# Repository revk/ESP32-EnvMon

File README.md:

# ESP32-EnvMon

Now at [Codeberg](https://codeberg.org/RevK/ESP32-EnvMon)

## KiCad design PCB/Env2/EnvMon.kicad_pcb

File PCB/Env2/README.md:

# EnvMon

These files are for use in [KiCad](https://www.kicad.org).

## Trademark

This is an open source project, but bear in mind you cannot sell boards bearing the Andrews & Arnold Ltd name, the A&A logo, the registered trademark AJK logo, or the GS1 allocated EANs assigned to Andrews & Arnold Ltd.

## Images

*Auto generated 2025-05-04T08:00:31*

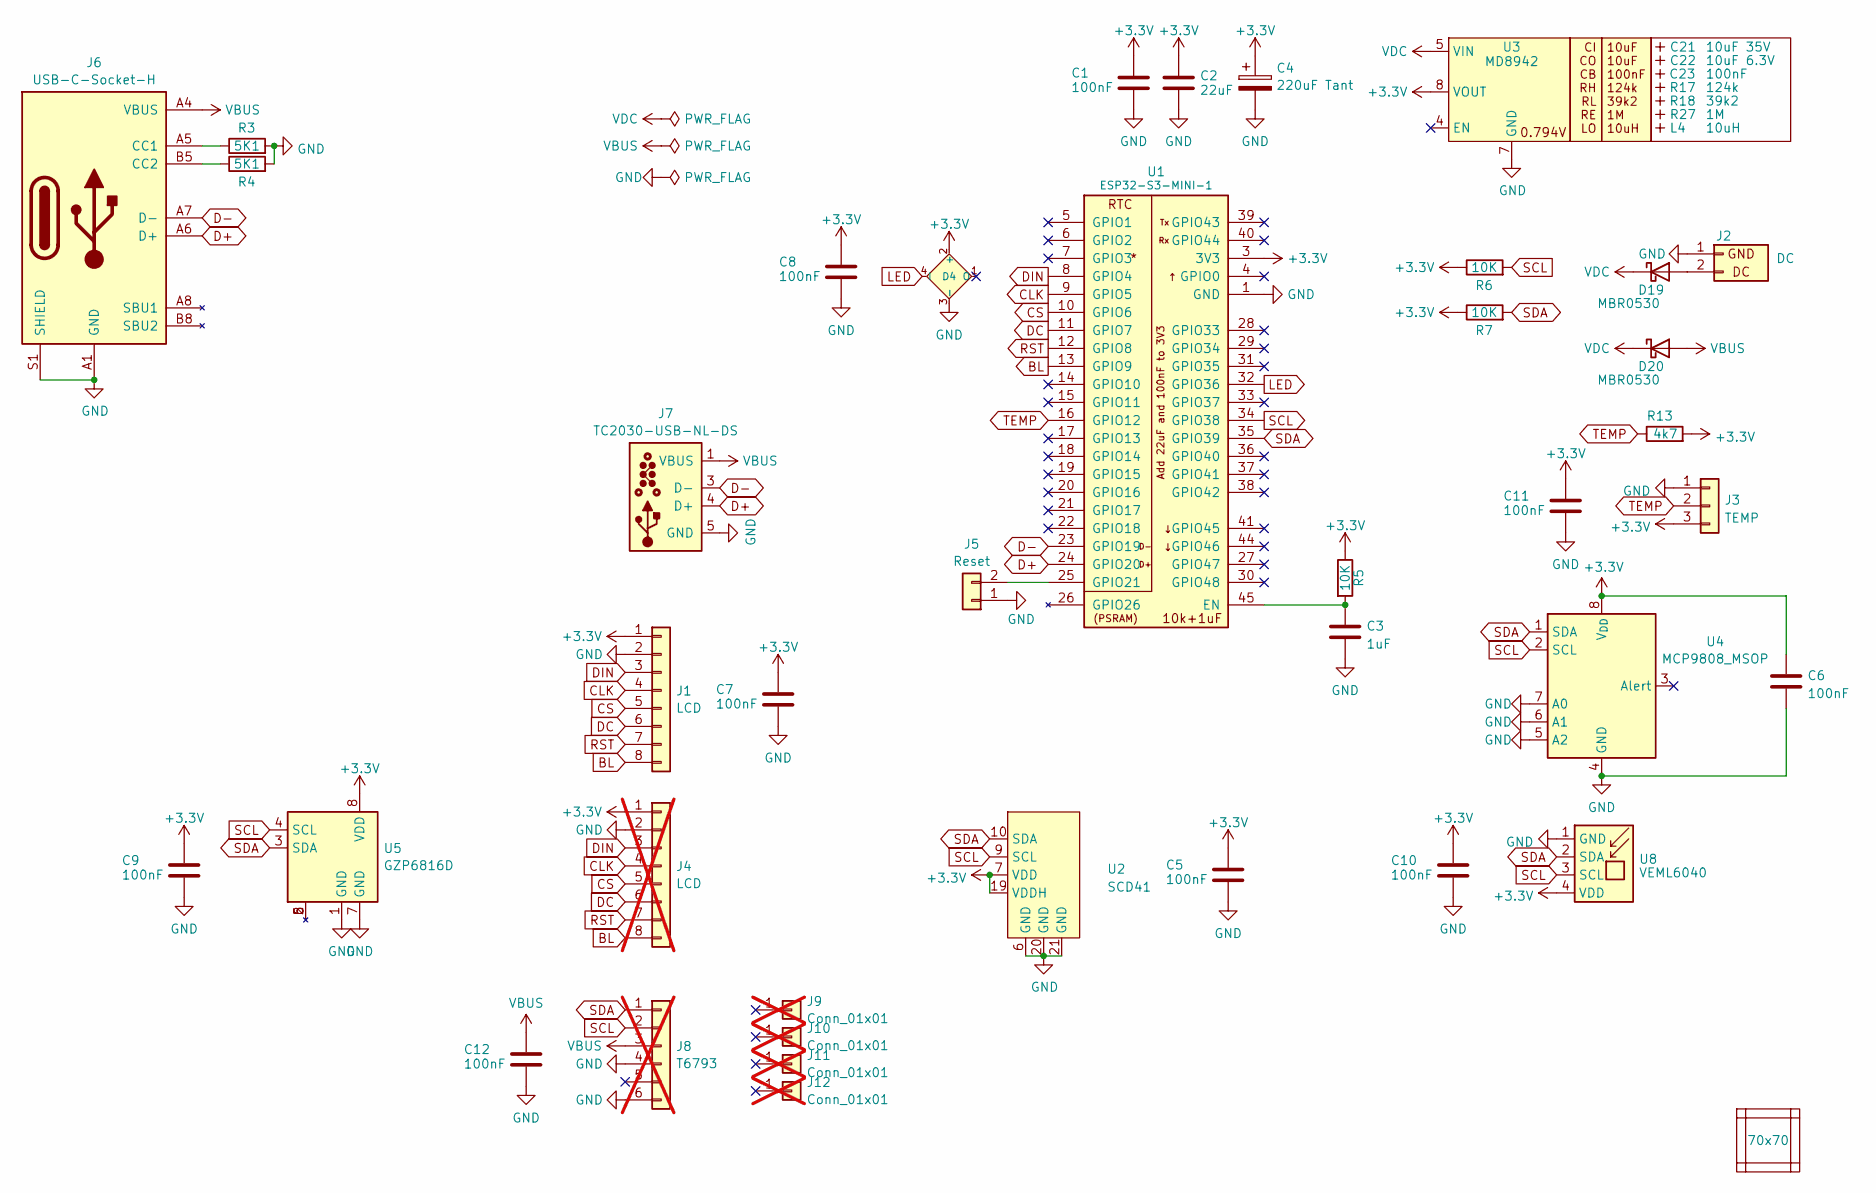
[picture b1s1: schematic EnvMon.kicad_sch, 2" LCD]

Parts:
C1, C5, C6, C7, C8, C9, C10, C11, C12: 100nF; C_0402
C2: 22uF; C_0402
C3: 1uF; C_0402
C4: 220uF Tant; CP_EIA-3528-21_Kemet-B; MPN C122649
C21: 10uF 35V; C_0603_; MPN C194427
C22: 10uF 6.3V; C_0603_; MPN C1691
C23: 100nF; C_0603_
D4: XL-1010RGBC-WS2812B; SMD1010-Side2; MPN C5349953
D19, D20: MBR0530; D_SOD-123; MPN C5204746
J1: LCD; LCD2; MPN C42380985
J2: DC; WAGO-2060-452-998-404; MPN C2765055
J3: TEMP; WAGO-2060-453-998-404; MPN C2765056
J4: LCD; PinHeader_1x08_P2.54mm_Vertical; MPN C42380985; not fitted
J5: Reset; AA-Pad
J6: USB-C-Socket-H; MPN C709357
J7: TC2030-USB-NL-DS; Tag-Connect_TC2030-IDC-NL_2x03_P1.27mm_Vertical
J8: T6793; PinHeader_1x06_P2.54mm_Vertical; not fitted
J9, J10, J11, J12: Conn_01x01; PinHeader_1x01_P2.54mm_Vertical; not fitted
L4: 10uH; L_4x4_; MPN C167879
PCB1: 70x70; PCB7070
R3, R4: 5K1; R_0402
R5, R6, R7: 10K; R_0402
R13: 4k7; R_0402
R17: 124k; R_0402_
R18: 39k2; R_0402_
R27: 1M; R_0402_
U1: ESP32-S3-MINI-1; MPN C3013941
U2: SCD41; MPN C3659294
U3: MD8942; SOT-23-6-MD8942; MPN C2684786
U4: MCP9808_MSOP; MSOP-8_3x3mm_P0.65mm-SIde; MPN C94847
U5: GZP6816D; Bosch_LGA-8_2x2.5mm_P0.65mm_ClockwisePinNumbering; MPN C3038127
U8: VEML6040; VEML6040-Side; MPN C78465
V1, V2, V3, V4: VCUT70

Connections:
+3.3V: C1.1, C2.1, C4.1, C5.1, C6.1, C7.1, C8.1, C9.1, C10.1, C11.1, D4.2 (+), J1.1, J3.3, J4.1, R5.1, R6.1, R7.1, R13.2, U1.3 (3V3), U2.7 (VDD), U2.19 (VDDH), U3.8 (VOUT), U4.8 (V_{DD}), U5.8 (VDD), U8.4 (VDD)
BL: J1.8, J4.8, U1.13 (GPIO9)
CLK: J1.4, J4.4, U1.9 (GPIO5)
CS: J1.5, J4.5, U1.10 (GPIO6)
D+: J6.A6 (D+), J6.B6 (D+), J7.4 (D+), U1.24 (GPIO20)
D-: J6.A7 (D-), J6.B7 (D-), J7.2 (NC), J7.3 (D-), J7.6 (NC), U1.23 (GPIO19)
DC: J1.6, J4.6, U1.11 (GPIO7)
DIN: J1.3, J4.3, U1.8 (GPIO4)
GND: C1.2, C2.2, C3.2, C4.2, C5.2, C6.2, C7.2, C8.2, C9.2, C10.2, C11.2, C12.2, D4.3 (-), J1.2, J2.1 (GND), J3.1, J4.2, J5.1, J6.A1 (GND), J6.A12 (GND), J6.B1 (GND), J6.B12 (GND), J6.S1 (SHIELD), J7.5 (GND), J8.4, J8.6, R3.2, R4.2, U1.1 (GND), U1.2 (GND), U1.42 (GND), U1.43 (GND), U1.46 (GND), U1.47 (GND), U1.48 (GND), U1.49 (GND), U1.50 (GND), U1.51 (GND), U1.52 (GND), U1.53 (GND), U1.54 (GND), U1.55 (GND), U1.56 (GND), U1.57 (GND), U1.58 (GND), U1.59 (GND), U1.60 (GND), U1.61 (GND), U1.62 (GND), U1.63 (GND), U1.64 (GND), U1.65 (GND), U2.6 (GND), U2.20 (GND), U2.21 (GND), U3.2 (GND), U3.7 (GND), U4.4 (GND), U4.5 (A2), U4.6 (A1), U4.7 (A0), U5.1 (GND), U5.7 (GND), U8.1 (GND)
LED: D4.4 (I), U1.32 (GPIO36)
unnamed: D19.2 (A), J2.2 (DC)
unnamed: J5.2, U1.25 (GPIO21)
unnamed: J6.A5 (CC1), R3.1
unnamed: J6.B5 (CC2), R4.1
unnamed: C3.1, R5.2, U1.45 (EN)
RST: J1.7, J4.7, U1.12 (GPIO8)
SCL: J8.2, R6.2, U1.34 (GPIO38), U2.9 (SCL), U4.2 (SCL), U5.4 (SCL), U8.3 (SCL)
SDA: J8.1, R7.2, U1.35 (GPIO39), U2.10 (SDA), U4.1 (SDA), U5.3 (SDA), U8.2 (SDA)
TEMP: J3.2, R13.1, U1.16 (GPIO12)
VBUS: C12.1, D20.2 (A), J6.A4 (VBUS), J6.A9 (VBUS), J6.B4 (VBUS), J6.B9 (VBUS), J7.1 (VBUS), J8.3
VDC: D19.1 (K), D20.1 (K), U3.5 (VIN)

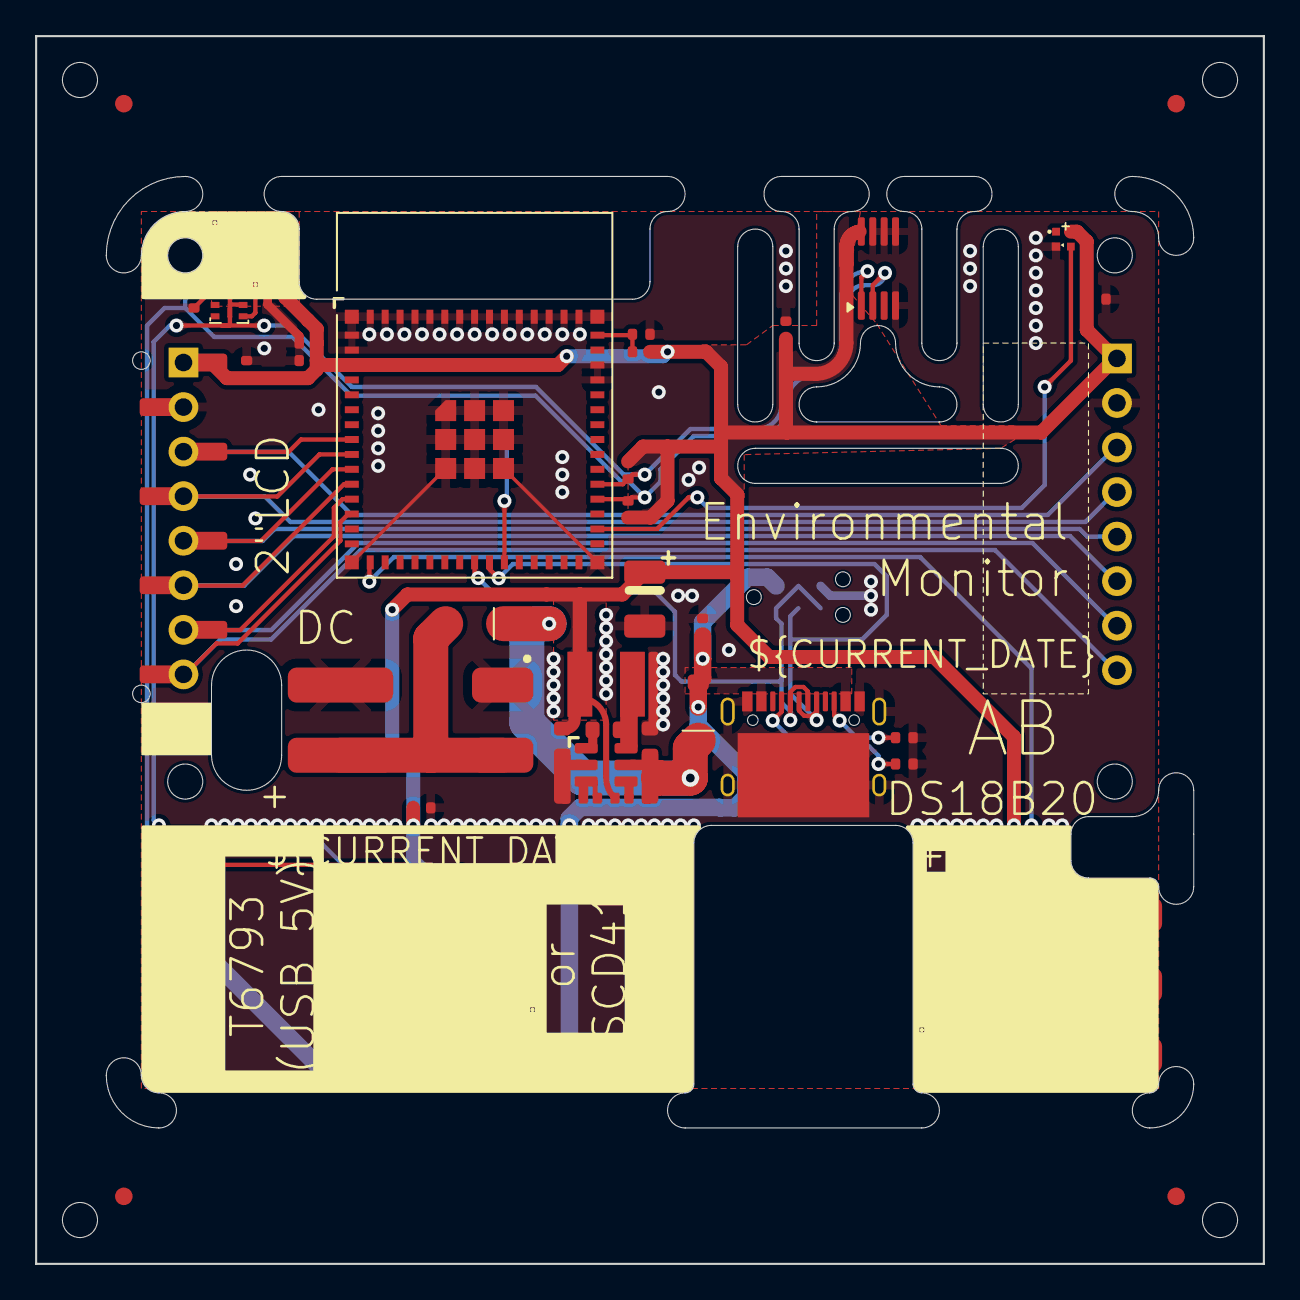
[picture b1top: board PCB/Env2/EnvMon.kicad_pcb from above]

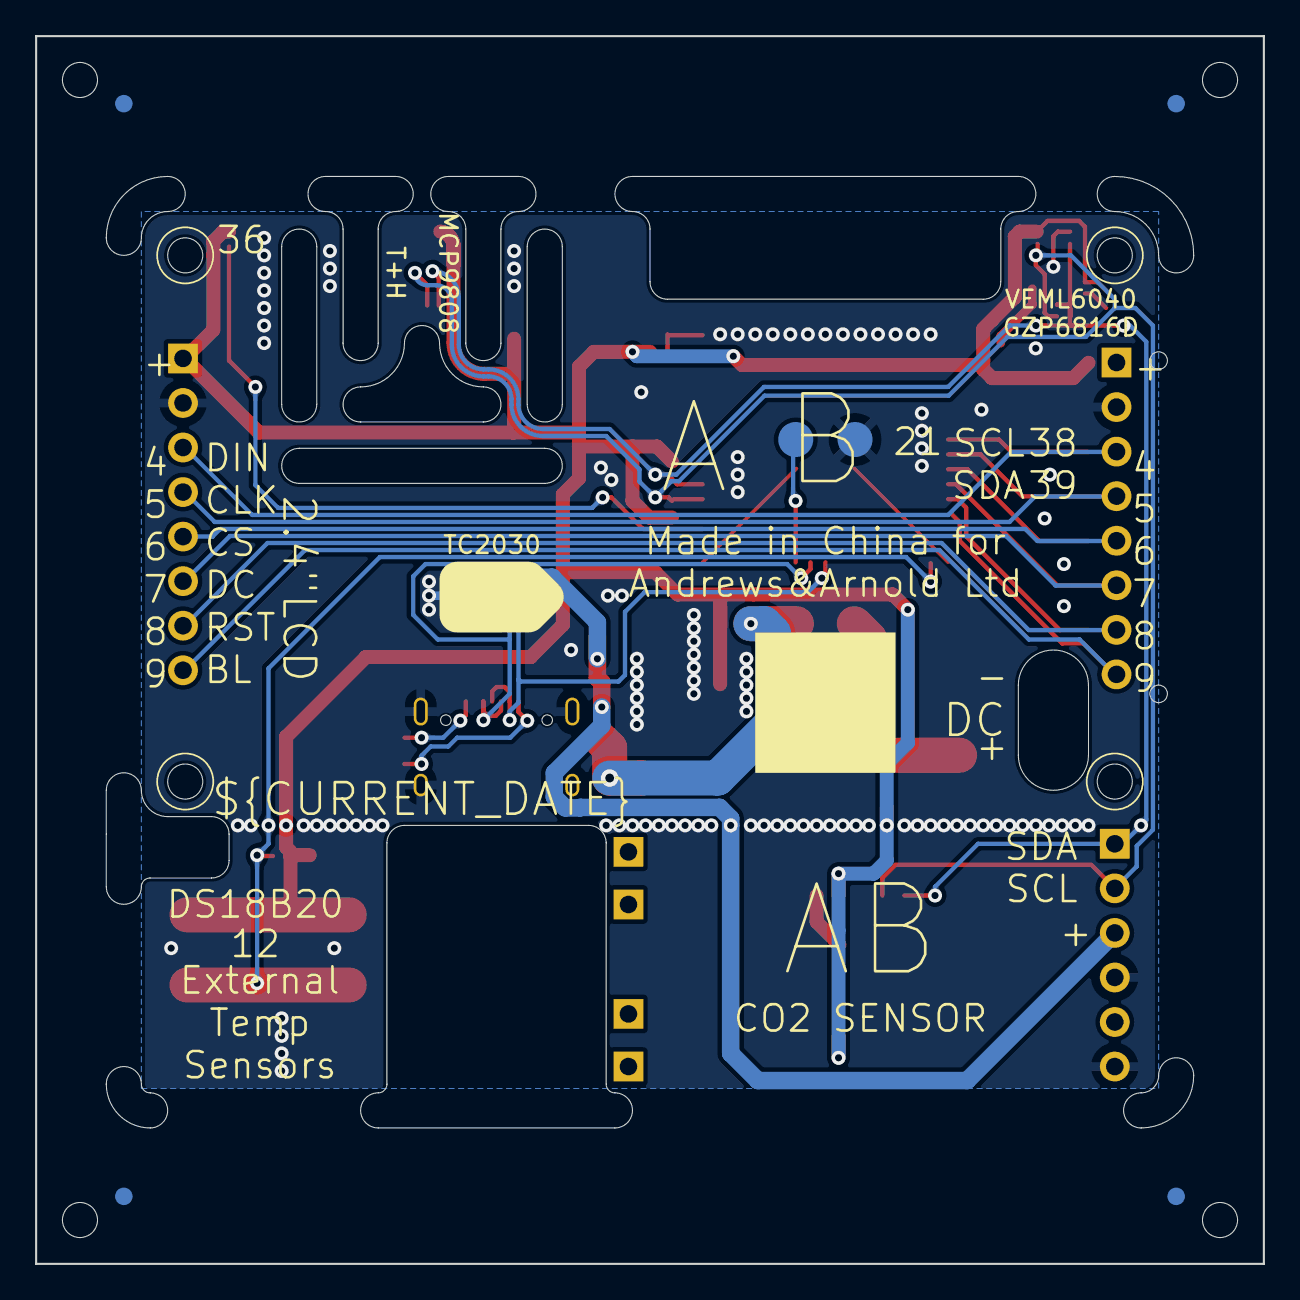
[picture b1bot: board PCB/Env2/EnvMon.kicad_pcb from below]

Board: 2 copper layers, 70.0 x 70.0 mm, 51 parts (3 on the bottom side), 21 nets.

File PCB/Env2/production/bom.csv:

Designator,Footprint,Quantity,Value,LCSC Part #
"C1, C10, C11, C12, C5, C6, C7, C8, C9",C_0402,9,100nF,
C2,C_0402,1,22uF,
C21,C_0603_,1,10uF 35V,C194427
C22,C_0603_,1,10uF 6.3V,C1691
C23,C_0603_,1,100nF,
C3,C_0402,1,1uF,
C4,CP_EIA-3528-21_Kemet-B,1,220uF Tant,C122649
"D19, D20",D_SOD-123,2,MBR0530,C5204746
D4,SMD1010,1,XL-1010RGBC-WS2812B,C5349953
J1,LCD2,1,LCD,C42380985
J2,WAGO-2060-452-998-404,1,DC,C2765055
J3,WAGO-2060-453-998-404,1,TEMP,C2765056
J6,USB-C-Socket-H,1,USB-C-Socket-H,C709357
L4,L_4x4_,1,10uH,C167879
R13,R_0402,1,4k7,
R17,R_0402_,1,124k,
R18,R_0402_,1,39k2,
R27,R_0402_,1,1M,
"R3, R4",R_0402,2,5K1,
"R5, R6, R7",R_0402,3,10K,
U1,ESP32-S3-MINI-1,1,ESP32-S3-MINI-1,C3013941
U2,SCD41,1,SCD41,C3659294
U3,SOT-23-6-MD8942,1,MD8942,C2684786
U4,MSOP-8_3x3mm_P0.65mm,1,MCP9808_MSOP,C94847
U5,Bosch_LGA-8_2x2.5mm_P0.65mm_ClockwisePinNumbering,1,GZP6816D,C3038127
U8,VEML6040,1,VEML6040,C78465

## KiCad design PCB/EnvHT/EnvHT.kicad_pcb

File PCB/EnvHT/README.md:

# EnvHT

These files are for use in [KiCad](https://www.kicad.org).

## Trademark

This is an open source project, but bear in mind you cannot sell boards bearing the Andrews & Arnold Ltd name, the A&A logo, the registered trademark AJK logo, or the GS1 allocated EANs assigned to Andrews & Arnold Ltd.

## Images

*Auto generated 2025-05-04T08:03:03*

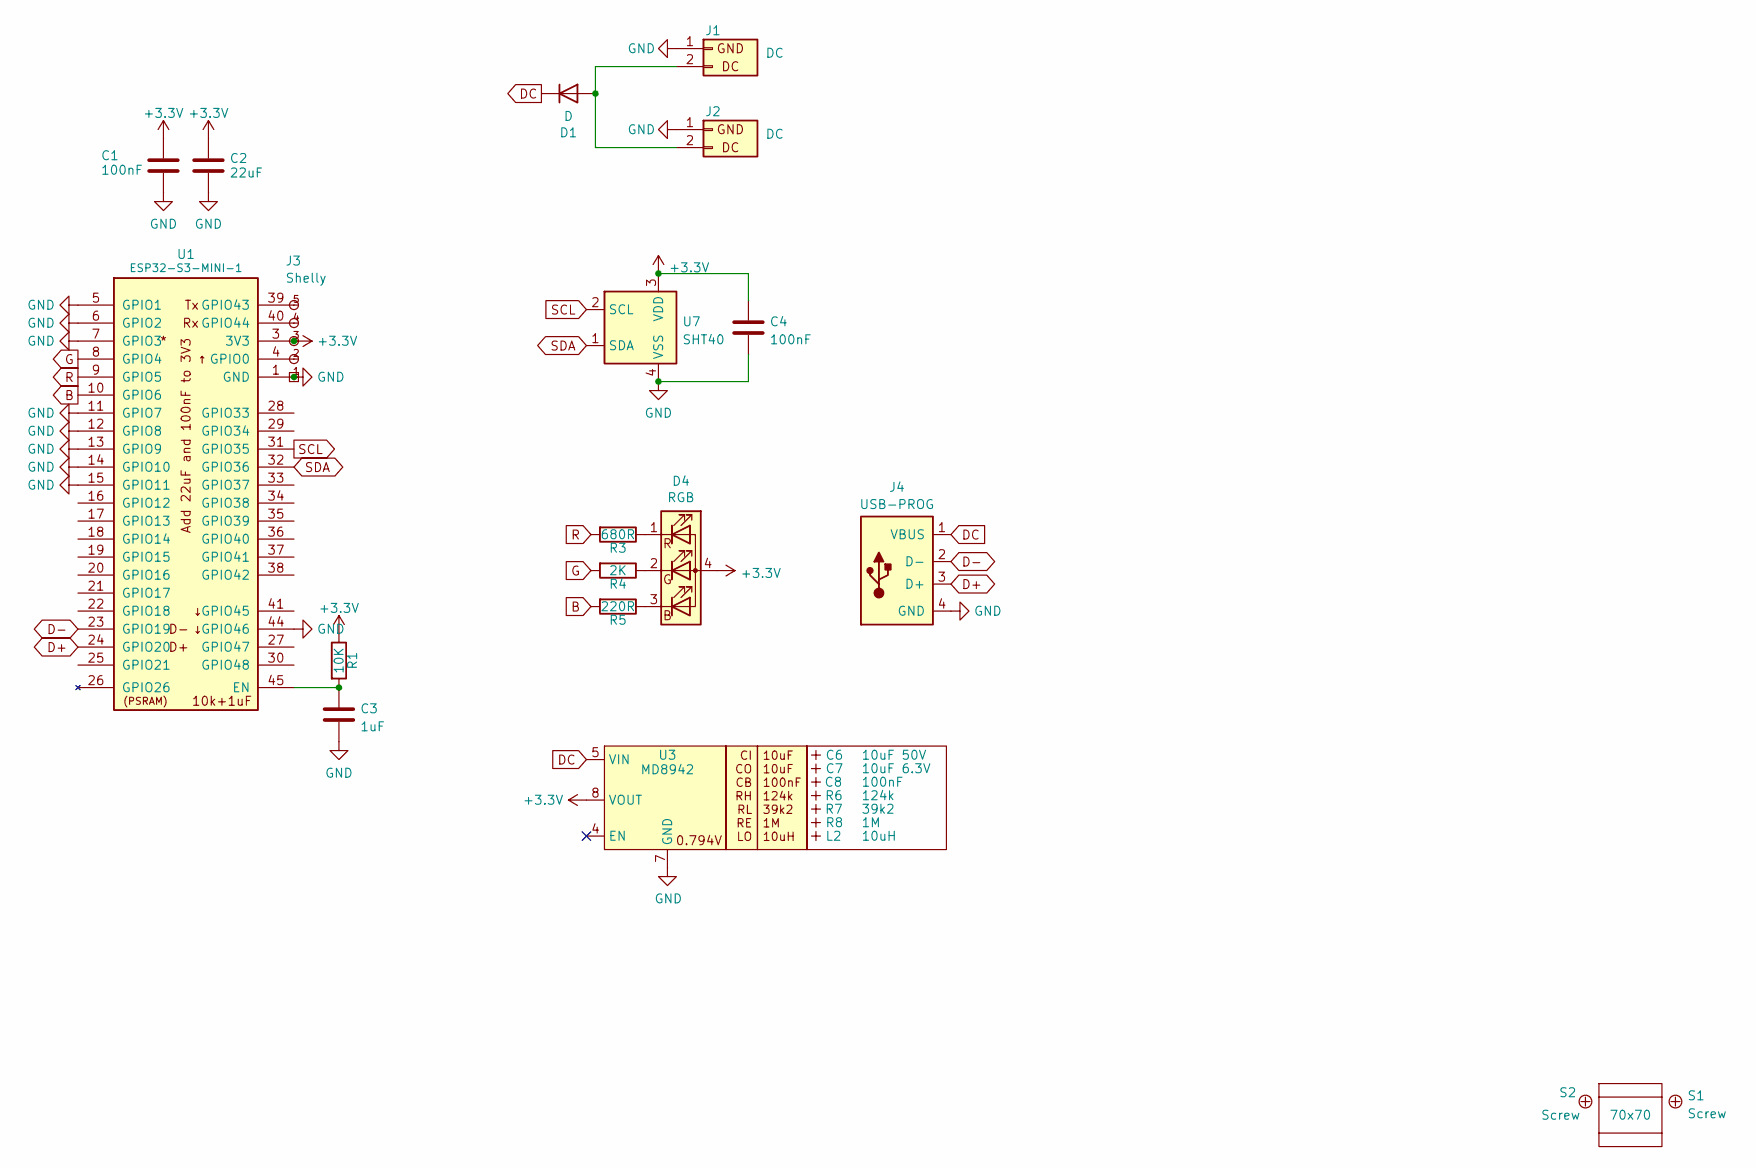
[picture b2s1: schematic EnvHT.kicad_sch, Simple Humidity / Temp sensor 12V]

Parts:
C1, C4: 100nF; C_0402
C2: 22uF; C_0603
C3: 1uF; C_0402
C6: 10uF 50V; C_0603_; MPN C1591
C7: 10uF 6.3V; C_0603_; MPN C1691
C8: 100nF; C_0603_
D1: D; D_SOD-123; MPN C1884542
D4: RGB; LED-RGB-1.6x1.6; Part No APTF1616LSEEZGKQBKC
J1, J2: DC; PTSM-HH1-2-RA
J3: Shelly
J4: USB-PROG
L2: 10uH; L_4x4_
PCB1: 70x70; PCB7070
R1: 10K; R_0402
R3: 680R; R_0402
R4: 2K; R_0402
R5: 220R; R_0402
R6: 124k; R_0402_
R7: 39k2; R_0402_
R8: 1M; R_0402_
S1, S2: Screw
U1: ESP32-S3-MINI-1; MPN C3013941
U3: MD8942; SOT-23-6-MD8942; MPN C2684786
U7: SHT40; Sensirion_DFN-4_1.5x1.5mm_P0.5mm_SHT4x; MPN C2909890
V2, V3: VCUT70

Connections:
+3.3V: C1.1, C2.1, C4.1, D4.4 (A), J3.3 (3V3), R1.1, U1.3 (3V3), U3.8 (VOUT), U7.3 (VDD)
B: R5.2, U1.10 (GPIO6)
D+: J4.3 (D+), U1.24 (GPIO20)
D-: J4.2 (D-), U1.23 (GPIO19)
DC: D1.1 (K), J4.1 (VBUS), U3.5 (VIN)
G: R4.2, U1.8 (GPIO4)
GND: C1.2, C2.2, C3.2, C4.2, J1.1 (GND), J2.1 (GND), J3.1 (GND), J4.4 (GND), U1.1 (GND), U1.2 (GND), U1.5 (GPIO1), U1.6 (GPIO2), U1.7 (GPIO3), U1.11 (GPIO7), U1.12 (GPIO8), U1.13 (GPIO9), U1.14 (GPIO10), U1.15 (GPIO11), U1.42 (GND), U1.43 (GND), U1.44 (GPIO46), U1.46 (GND), U1.47 (GND), U1.48 (GND), U1.49 (GND), U1.50 (GND), U1.51 (GND), U1.52 (GND), U1.53 (GND), U1.54 (GND), U1.55 (GND), U1.56 (GND), U1.57 (GND), U1.58 (GND), U1.59 (GND), U1.60 (GND), U1.61 (GND), U1.62 (GND), U1.63 (GND), U1.64 (GND), U1.65 (GND), U3.2 (GND), U3.7 (GND), U7.4 (VSS)
unnamed: D1.2 (A), J1.2 (DC), J2.2 (DC)
unnamed: D4.3 (BK), R5.1
unnamed: D4.2 (GK), R4.1
unnamed: D4.1 (RK), R3.1
unnamed: J3.2 (0), U1.4 (GPIO0)
unnamed: J3.4 (Rx), U1.40 (GPIO44)
unnamed: J3.5 (Tx), U1.39 (GPIO43)
unnamed: C3.1, R1.2, U1.45 (EN)
R: R3.2, U1.9 (GPIO5)
SCL: U1.31 (GPIO35), U7.2 (SCL)
SDA: U1.32 (GPIO36), U7.1 (SDA)

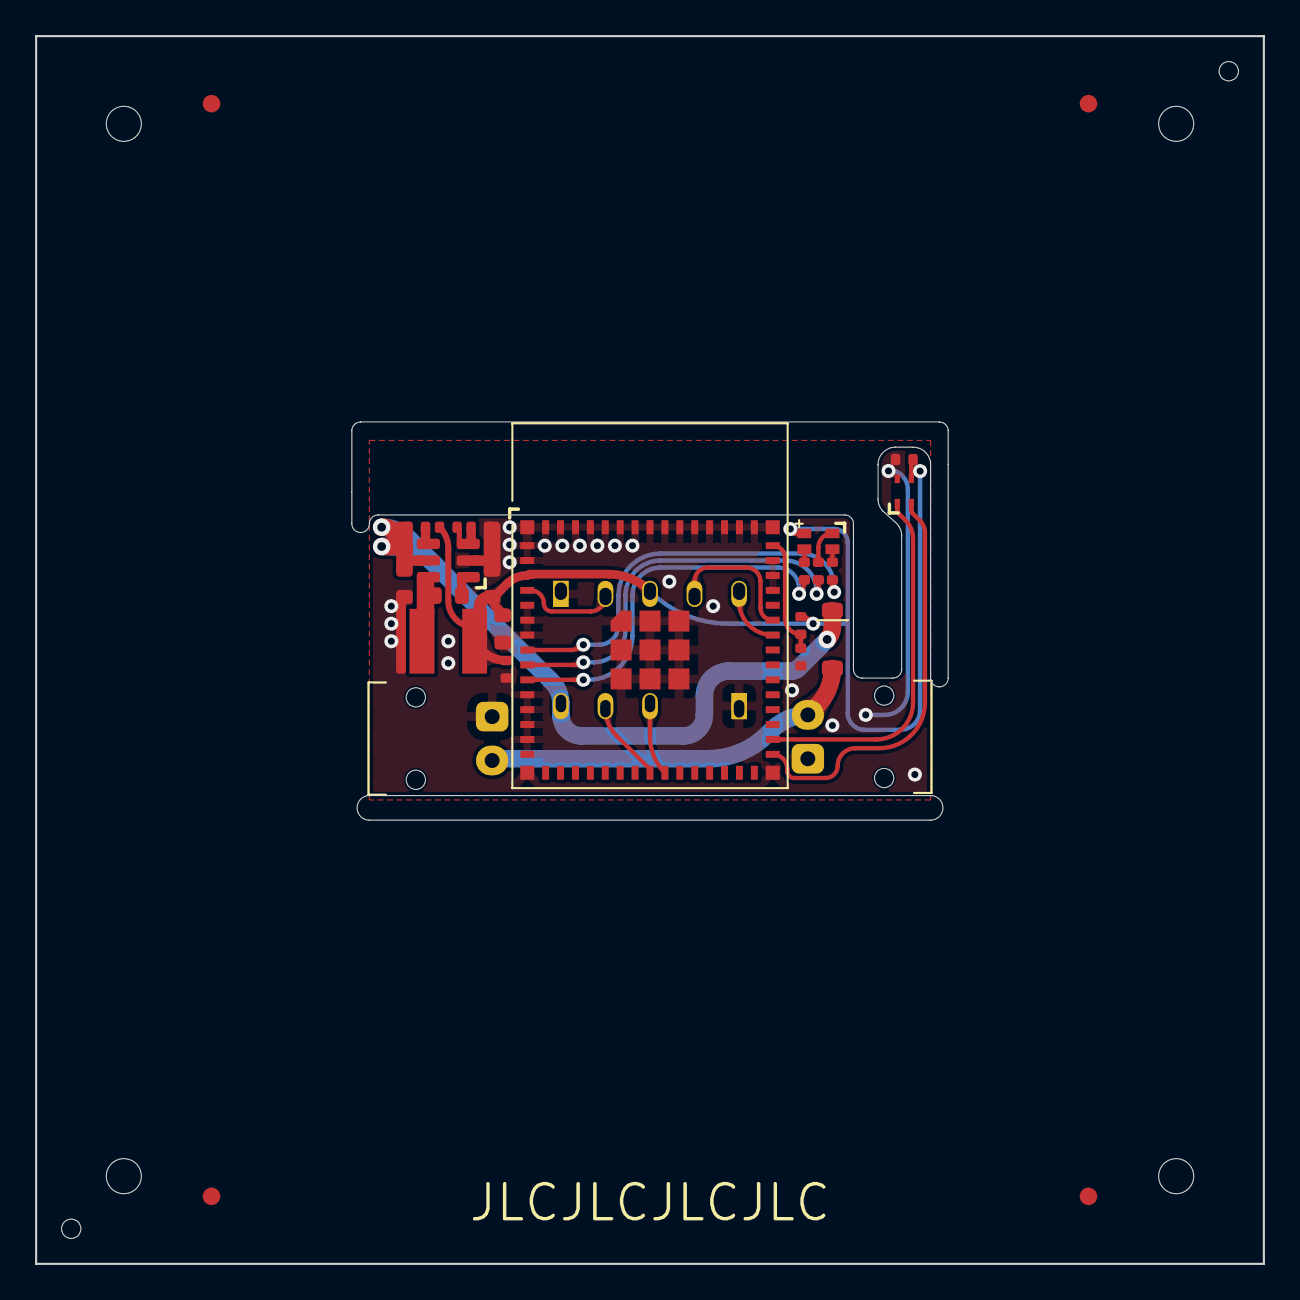
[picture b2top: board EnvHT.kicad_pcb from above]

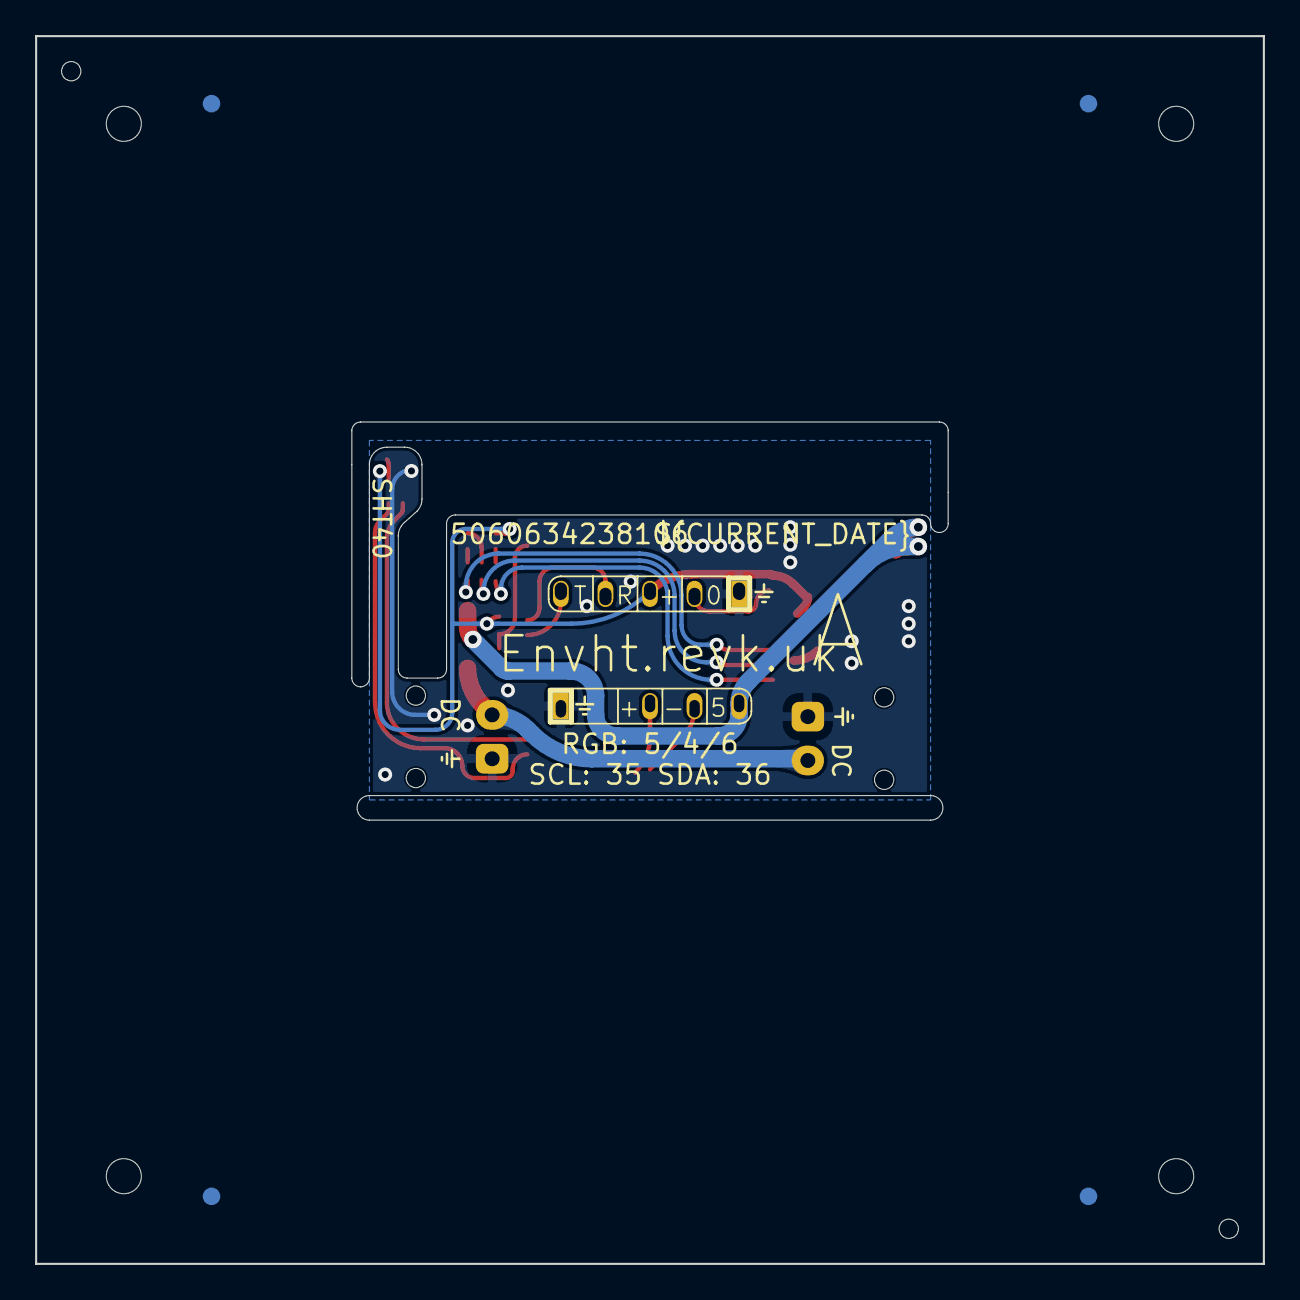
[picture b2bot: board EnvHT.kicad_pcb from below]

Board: 2 copper layers, 70.0 x 70.0 mm, 29 parts (2 on the bottom side), 18 nets.

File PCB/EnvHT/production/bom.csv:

Designator,Footprint,Quantity,Value,LCSC Part #
"C1, C4",C_0402,2,100nF,
C2,C_0603,1,22uF,
C3,C_0402,1,1uF,
C6,C_0603_,1,10uF 50V,C1591
C7,C_0603_,1,10uF 6.3V,C1691
C8,C_0603_,1,100nF,
D1,D_SOD-123,1,D,C1884542
D4,LED-RGB-1.6x1.6,1,RGB,C264508
J4,USB-PROG,1,USB-PROG,
L2,L_4x4_,1,10uH,
R1,R_0402,1,10K,
R3,R_0402,1,680R,
R4,R_0402,1,2K,
R5,R_0402,1,220R,
R6,R_0402_,1,124k,
R7,R_0402_,1,39k2,
R8,R_0402_,1,1M,
U1,ESP32-S3-MINI-1,1,ESP32-S3-MINI-1,C3013941
U3,SOT-23-6-MD8942,1,MD8942,C2684786
U7,Sensirion_DFN-4_1.5x1.5mm_P0.5mm_SHT4x,1,SHT40,C2909890

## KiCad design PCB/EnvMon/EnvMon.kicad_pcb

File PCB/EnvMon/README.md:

# EnvMon

These files are for use in [KiCad](https://www.kicad.org).

## Trademark

This is an open source project, but bear in mind you cannot sell boards bearing the Andrews & Arnold Ltd name, the A&A logo, the registered trademark AJK logo, or the GS1 allocated EANs assigned to Andrews & Arnold Ltd.

## Images

*Auto generated 2025-05-04T08:05:16*

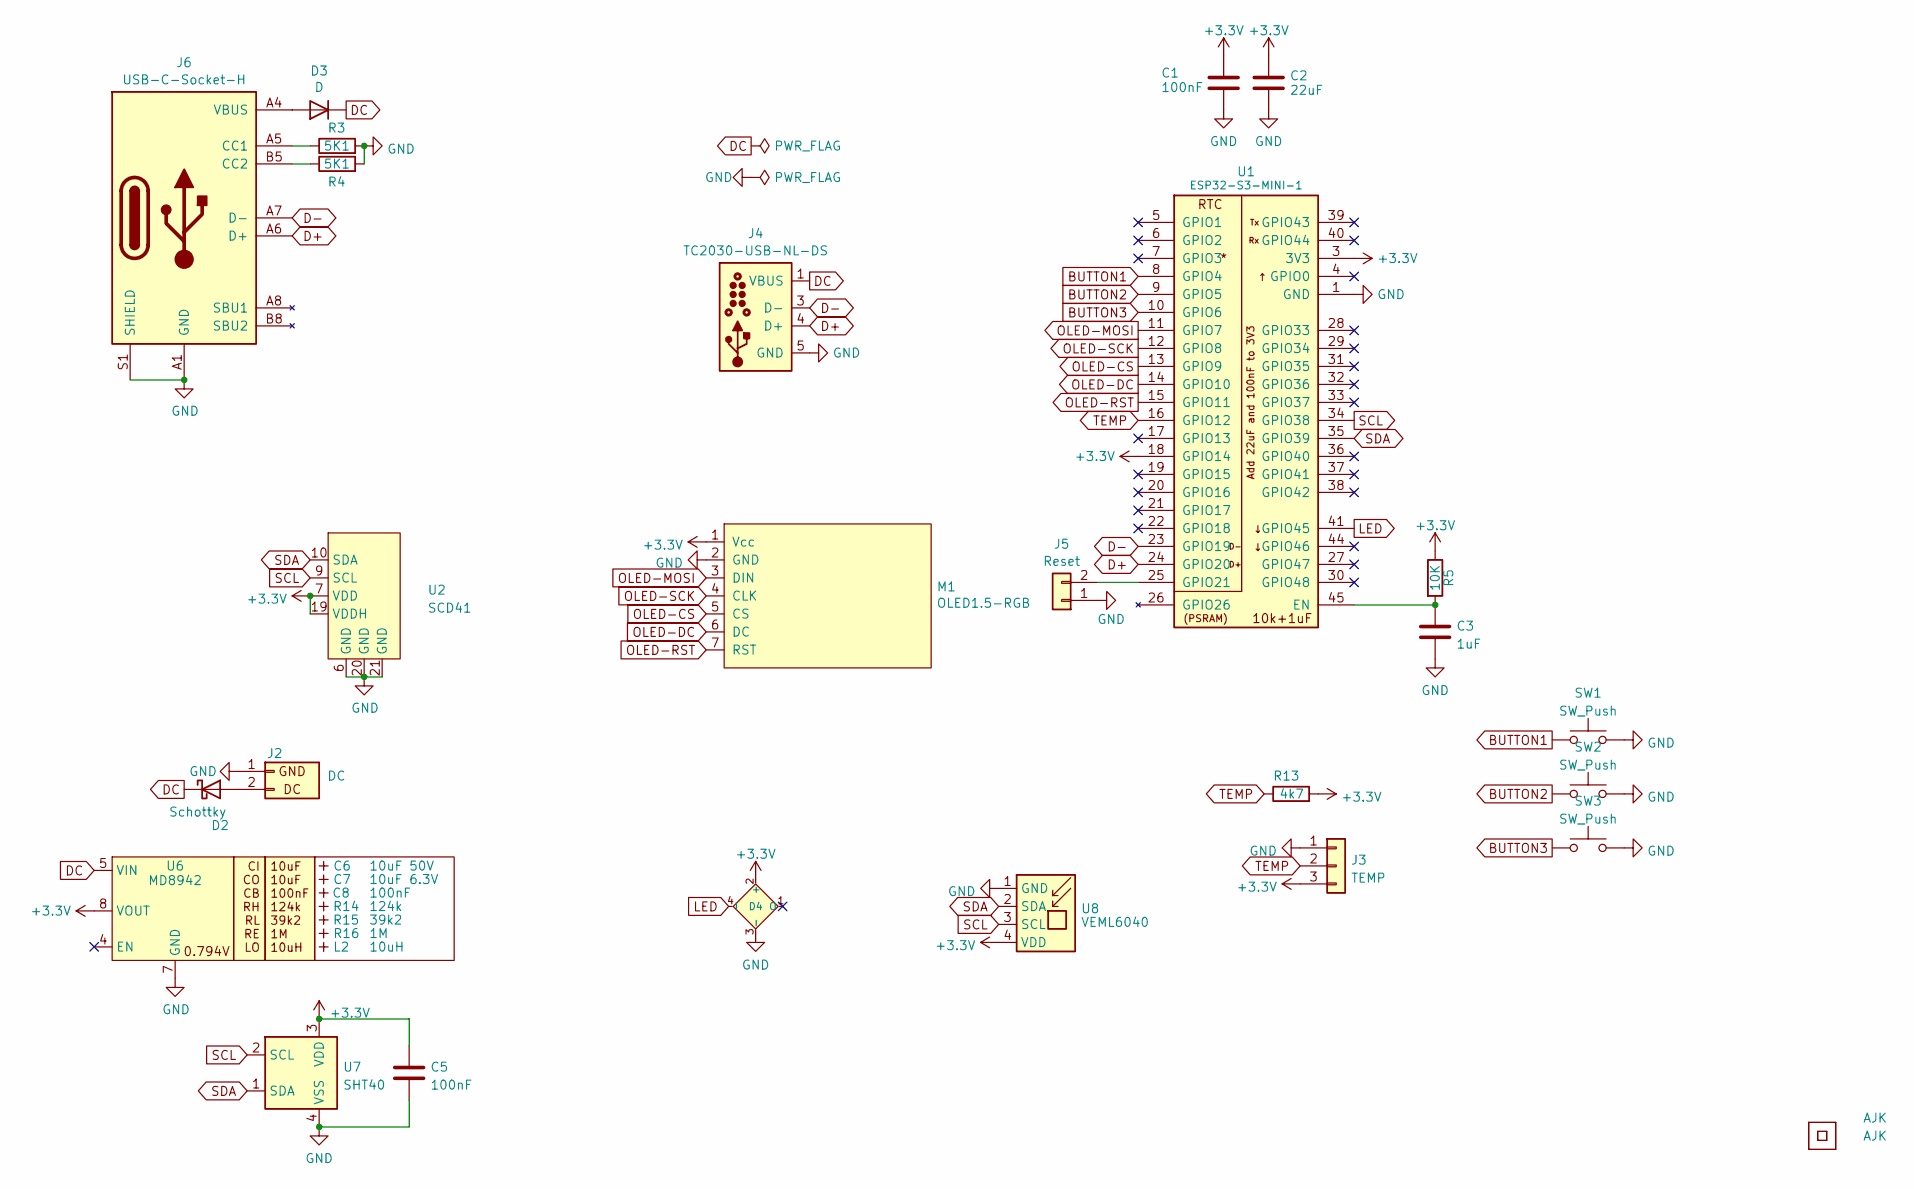
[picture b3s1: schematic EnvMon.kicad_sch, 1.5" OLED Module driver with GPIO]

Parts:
C1, C5: 100nF; C_0402
C2: 22uF; C_0402
C3: 1uF; C_0402
C6: 10uF 50V; C_0603_; MPN C1591
C7: 10uF 6.3V; C_0603_; MPN C1691
C8: 100nF; C_0603_
D2: Schottky; D_1206; MPN C143805
D3: D; D_SOD-123; MPN C1884542
D4: XL-1010RGBC-WS2812B; SMD1010; MPN C5349953
J2: DC; WAGO-2060-452-998-404
J3: TEMP; WAGO-2060-453-998-404
J4: TC2030-USB-NL-DS; Tag-Connect_TC2030-IDC-NL_2x03_P1.27mm_Vertical
J5: Reset; AA-Pad
J6: USB-C-Socket-H; MPN C709357
L2: 10uH; L_4x4_
Logo1, Logo2: AJK
M1: OLED1.5-RGB
R3, R4: 5K1; R_0402
R5: 10K; R_0402
R13: 4k7; R_0402
R14: 124k; R_0402_
R15: 39k2; R_0402_
R16: 1M; R_0402_
SW1, SW2, SW3: SW_Push; SW_PUSH_6mm_H13mm
U1: ESP32-S3-MINI-1; MPN C3013941
U2: SCD41
U5: QR; QR-ENVMON
U6: MD8942; SOT-23-6-MD8942; MPN C2684786
U7: SHT40; Sensirion_DFN-4_1.5x1.5mm_P0.5mm_SHT4x; MPN C2909890
U8: VEML6040; MPN C78465

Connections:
+3.3V: C1.1, C2.1, C5.1, D4.2 (+), J3.3, M1.1 (Vcc), R5.1, R13.2, U1.3 (3V3), U1.18 (GPIO14), U2.7 (VDD), U2.19 (VDDH), U6.8 (VOUT), U7.3 (VDD), U8.4 (VDD)
BUTTON1: SW1.1, U1.8 (GPIO4)
BUTTON2: SW2.1, U1.9 (GPIO5)
BUTTON3: SW3.1, U1.10 (GPIO6)
D+: J4.4 (D+), J6.A6 (D+), J6.B6 (D+), U1.24 (GPIO20)
D-: J4.3 (D-), J6.A7 (D-), J6.B7 (D-), U1.23 (GPIO19)
DC: D2.1 (K), D3.1 (K), J4.1 (VBUS), J4.2 (VBUS), U6.5 (VIN)
GND: C1.2, C2.2, C3.2, C5.2, D4.3 (-), J2.1 (GND), J3.1, J4.5 (GND), J4.6 (GND), J5.1, J6.A1 (GND), J6.A12 (GND), J6.B1 (GND), J6.B12 (GND), J6.S1 (SHIELD), M1.2 (GND), R3.2, R4.2, SW1.2, SW2.2, SW3.2, U1.1 (GND), U1.2 (GND), U1.42 (GND), U1.43 (GND), U1.46 (GND), U1.47 (GND), U1.48 (GND), U1.49 (GND), U1.50 (GND), U1.51 (GND), U1.52 (GND), U1.53 (GND), U1.54 (GND), U1.55 (GND), U1.56 (GND), U1.57 (GND), U1.58 (GND), U1.59 (GND), U1.60 (GND), U1.61 (GND), U1.62 (GND), U1.63 (GND), U1.64 (GND), U1.65 (GND), U2.6 (GND), U2.20 (GND), U2.21 (GND), U6.2 (GND), U6.7 (GND), U7.4 (VSS), U8.1 (GND)
LED: D4.4 (I), U1.41 (GPIO45)
unnamed: D2.2 (A), J2.2 (DC)
unnamed: D3.2 (A), J6.A4 (VBUS), J6.A9 (VBUS), J6.B4 (VBUS), J6.B9 (VBUS)
unnamed: J5.2, U1.25 (GPIO21)
unnamed: J6.A5 (CC1), R3.1
unnamed: J6.B5 (CC2), R4.1
unnamed: C3.1, R5.2, U1.45 (EN)
OLED-CS: M1.5 (CS), U1.13 (GPIO9)
OLED-DC: M1.6 (DC), U1.14 (GPIO10)
OLED-MOSI: M1.3 (DIN), U1.11 (GPIO7)
OLED-RST: M1.7 (RST), U1.15 (GPIO11)
OLED-SCK: M1.4 (CLK), U1.12 (GPIO8)
SCL: U1.34 (GPIO38), U2.9 (SCL), U7.2 (SCL), U8.3 (SCL)
SDA: U1.35 (GPIO39), U2.10 (SDA), U7.1 (SDA), U8.2 (SDA)
TEMP: J3.2, R13.1, U1.16 (GPIO12)

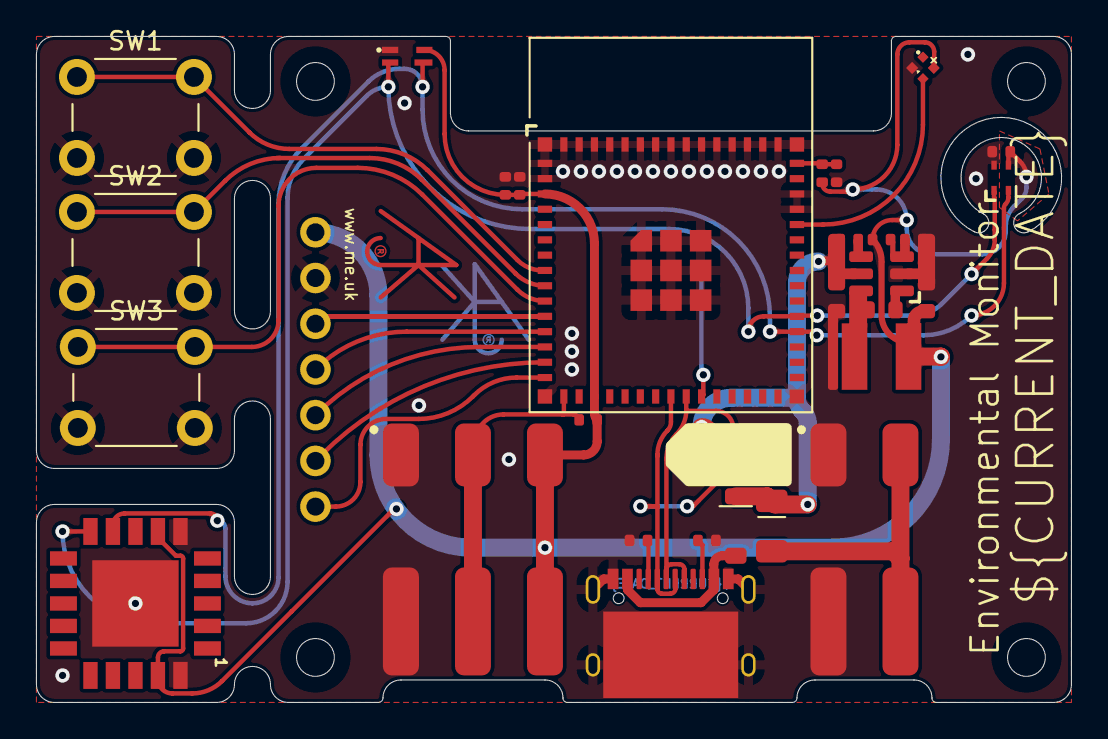
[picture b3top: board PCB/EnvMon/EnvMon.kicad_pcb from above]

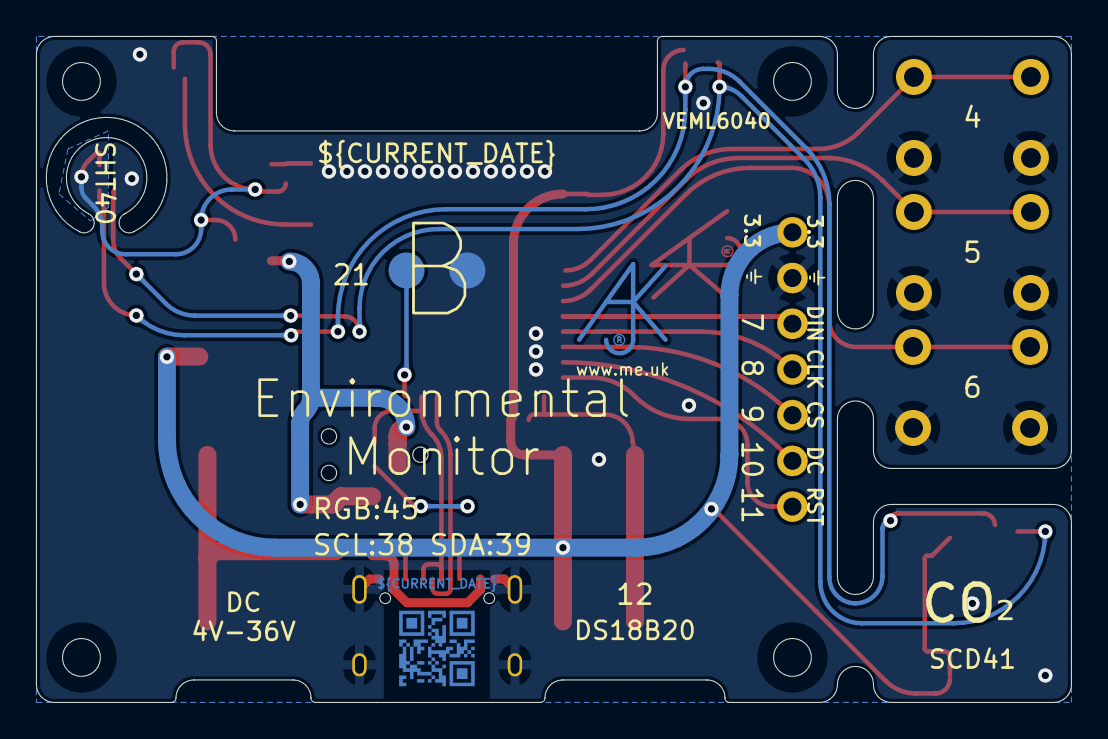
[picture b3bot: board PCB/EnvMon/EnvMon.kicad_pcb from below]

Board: 4 copper layers, 57.5 x 37.0 mm, 35 parts (3 on the bottom side), 23 nets.

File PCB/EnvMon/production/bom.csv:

Designator,Footprint,Quantity,Value,LCSC Part #
"C1, C5",C_0402,2,100nF,
C2,C_0402,1,22uF,
C3,C_0402,1,1uF,
C6,C_0603_,1,10uF 50V,C1591
C7,C_0603_,1,10uF 6.3V,C1691
C8,C_0603_,1,100nF,
D2,D_1206,1,Schottky,C143805
D3,D_SOD-123,1,D,C1884542
D4,SMD1010,1,XL-1010RGBC-WS2812B,C5349953
J2,WAGO-2060-452-998-404,1,DC,
J3,WAGO-2060-453-998-404,1,TEMP,
J5,AA-Pad,1,Reset,
J6,USB-C-Socket-H,1,USB-C-Socket-V,C709357
L2,L_4x4_,1,10uH,
M1,OLED1.5-RGB,1,OLED1.5-RGB,
R13,R_0402,1,4k7,
R14,R_0402_,1,124k,
R15,R_0402_,1,39k2,
R16,R_0402_,1,1M,
"R3, R4",R_0402,2,5K1,
R5,R_0402,1,10K,
"SW1, SW2, SW3",SW_PUSH_6mm_H13mm,3,SW_Push,
U1,ESP32-S3-MINI-1,1,ESP32-S3-MINI-1,C3013941
U2,SCD41,1,SCD41,
U6,SOT-23-6-MD8942,1,MD8942,C2684786
U7,Sensirion_DFN-4_1.5x1.5mm_P0.5mm_SHT4x,1,SHT40,C2909890
U8,VEML6040,1,VEML6040,C78465
